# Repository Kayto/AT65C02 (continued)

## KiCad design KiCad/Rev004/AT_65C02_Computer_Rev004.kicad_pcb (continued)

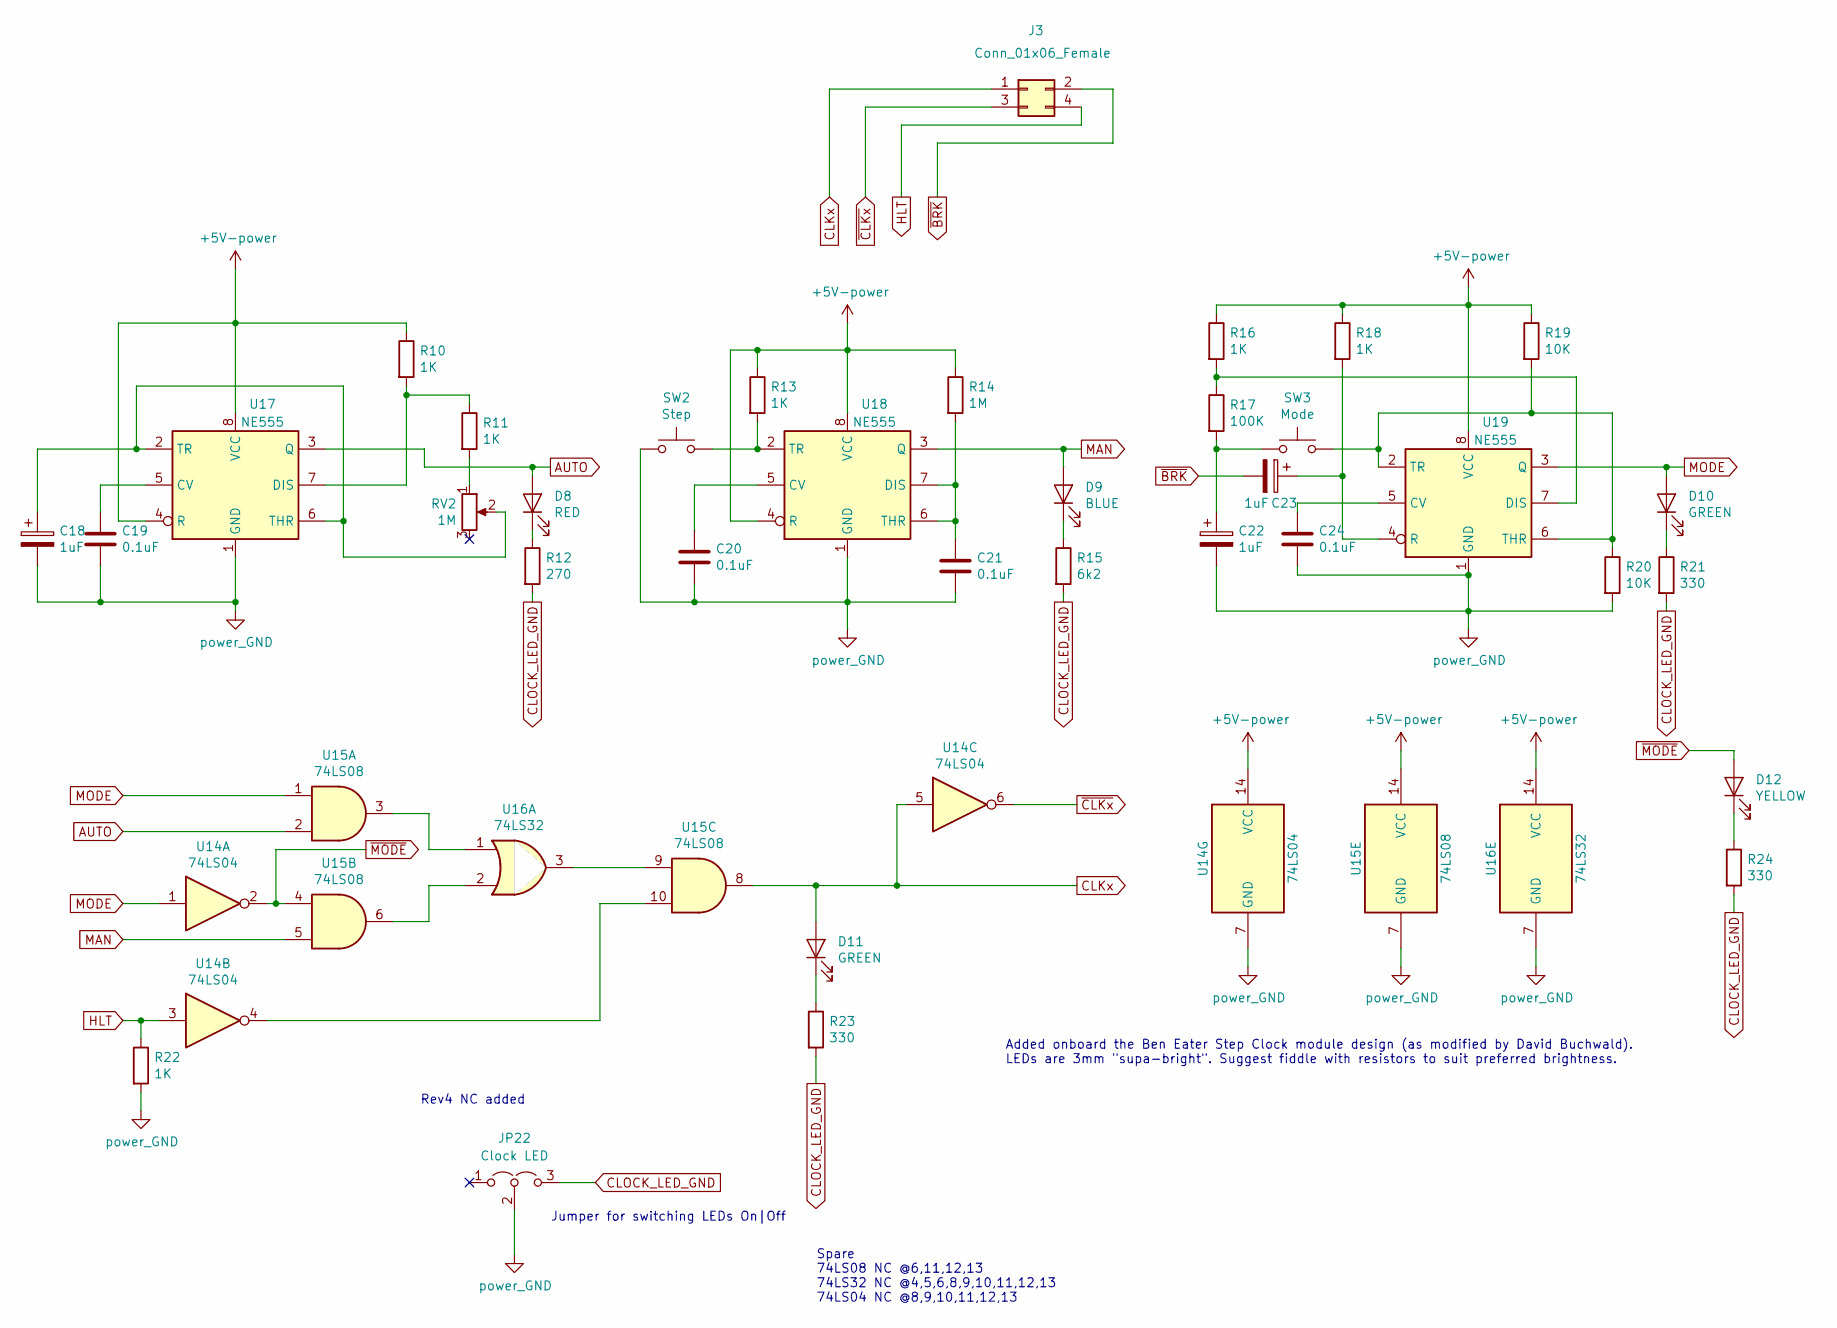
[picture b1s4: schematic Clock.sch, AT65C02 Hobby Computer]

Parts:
C18, C22, C23: 1uF; CP_Radial_D5.0mm_P2.50mm
C19, C20, C21, C24: 0.1uF; C_Disc_D3.4mm_W2.1mm_P2.50mm
D8: RED; LED_D3.0mm
D9: BLUE; LED_D3.0mm
D10, D11: GREEN; LED_D3.0mm
D12: YELLOW; LED_D3.0mm
J3: Conn_01x06_Female; PinSocket_2x02_P2.54mm_Vertical
JP22: Clock LED; PinHeader_1x03_P2.54mm_Vertical
R10, R11, R13, R16, R18, R22: 1K; R_Axial_DIN0207_L6.3mm_D2.5mm_P7.62mm_Horizontal
R12: 270; R_Axial_DIN0207_L6.3mm_D2.5mm_P7.62mm_Horizontal
R14: 1M; R_Axial_DIN0207_L6.3mm_D2.5mm_P7.62mm_Horizontal
R15: 6k2; R_Axial_DIN0207_L6.3mm_D2.5mm_P7.62mm_Horizontal
R17: 100K; R_Axial_DIN0207_L6.3mm_D2.5mm_P7.62mm_Horizontal
R19, R20: 10K; R_Axial_DIN0207_L6.3mm_D2.5mm_P7.62mm_Horizontal
R21, R23, R24: 330; R_Axial_DIN0207_L6.3mm_D2.5mm_P7.62mm_Horizontal
RV2: 1M; Potentiometer_Piher_PT-10-V10_Vertical
SW2: Step; SW_PUSH_6mm
SW3: Mode; SW_PUSH_6mm
U14: 74LS04; DIP-14_W7.62mm_Socket
U15: 74LS08; DIP-14_W7.62mm_Socket
U16: 74LS32; DIP-14_W7.62mm_Socket
U17, U18, U19: NE555; DIP-8_W7.62mm_Socket

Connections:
AUTO: D8.2 (A), U15.2, U17.3 (Q)
CLKx: D11.2 (A), J3.1, U14.5, U15.8; also elsewhere on the board
CLOCK_LED_GND: JP22.3 (B), R12.2, R15.2, R21.2, R23.2, R24.2
HLT: J3.4, R22.1, U14.3
MAN: D9.2 (A), U15.5, U18.3 (Q)
MODE: D10.2 (A), U14.1, U15.1, U19.3 (Q)
unnamed: C18.1, RV2.2, U17.2 (TR), U17.6 (THR)
unnamed: C19.1, U17.5 (CV)
unnamed: C20.1, U18.5 (CV)
unnamed: C21.1, R14.2, U18.6 (THR), U18.7 (DIS)
unnamed: C22.1, R17.2, SW3.1
unnamed: C23.1, R18.2, U19.4 (R)
unnamed: C24.1, U19.5 (CV)
unnamed: D8.1 (K), R12.1
unnamed: D9.1 (K), R15.1
unnamed: D10.1 (K), R21.1
unnamed: D11.1 (K), R23.1
unnamed: D12.1 (K), R24.1
unnamed: R10.2, R11.1, U17.7 (DIS)
unnamed: R11.2, RV2.1
unnamed: R13.2, SW2.2, U18.2 (TR)
unnamed: R16.2, R17.1, U19.7 (DIS)
unnamed: R19.2, R20.1, SW3.2, U19.2 (TR), U19.6 (THR)
unnamed: U14.4, U15.10
unnamed: U15.3, U16.1
unnamed: U15.6, U16.2
unnamed: U15.9, U16.3
~BRK: C23.2, J3.2
~CLKx: J3.3, U14.6
~MODE: D12.2 (A), U14.2, U15.4

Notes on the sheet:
Added onboard the Ben Eater Step Clock module design (as modified by David Buchwald). LEDs are 3mm "supa-bright". Suggest fiddle with resistors to suit preferred brightness.
Jumper for switching LEDs On|Off
Spare 74LS08 NC @6,11,12,13 74LS32 NC @4,5,6,8,9,10,11,12,13 74LS04 NC @8,9,10,11,12,13
Rev4 NC added

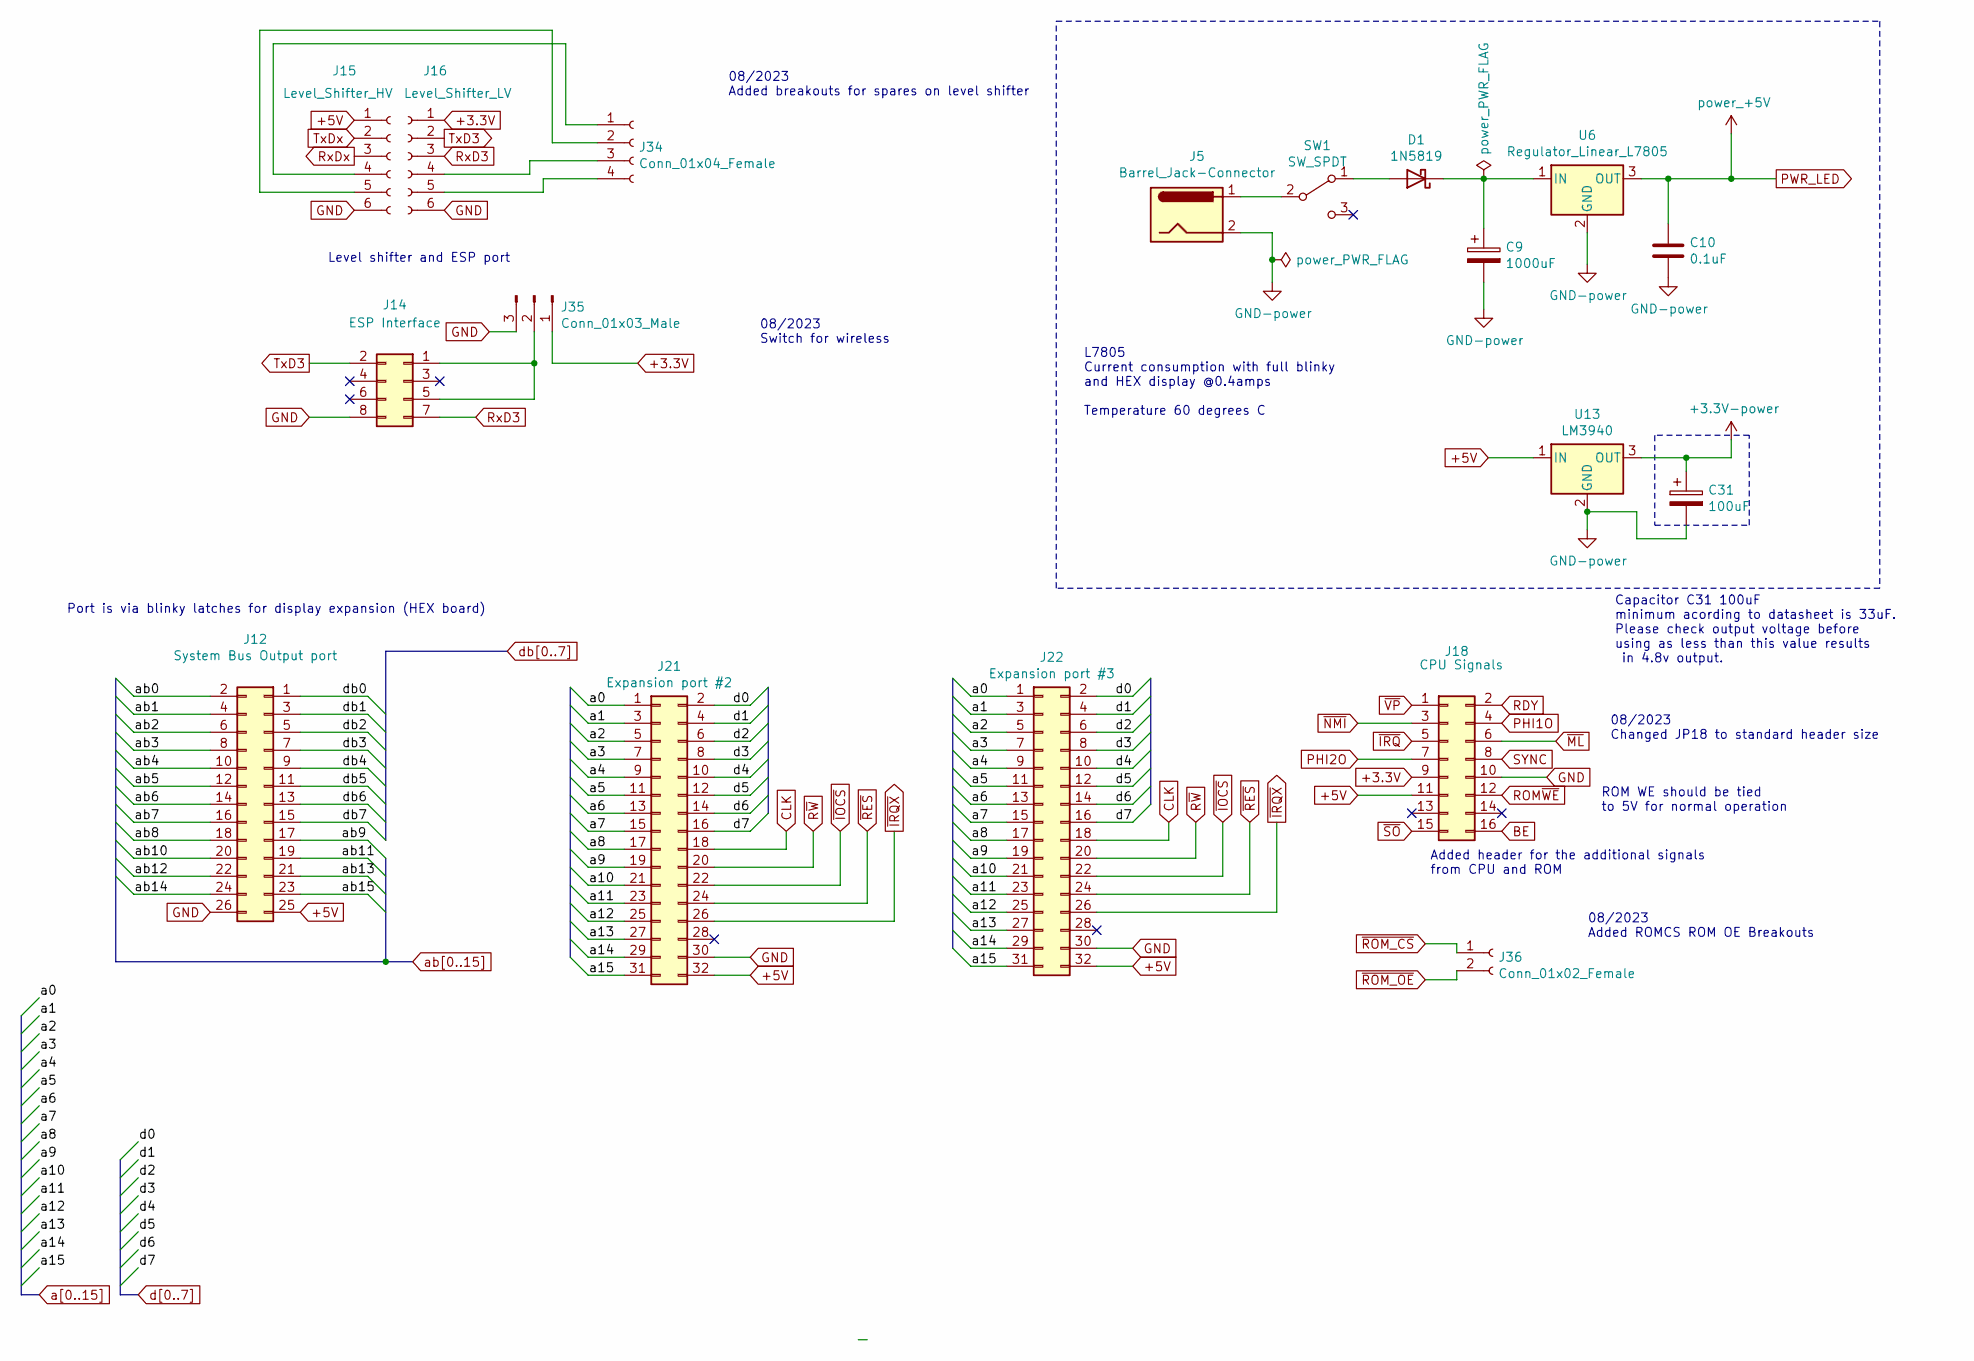
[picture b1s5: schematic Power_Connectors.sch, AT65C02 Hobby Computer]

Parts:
C9: 1000uF; CP_Radial_D10.0mm_P5.00mm
C10: 0.1uF; C_Disc_D3.4mm_W2.1mm_P2.50mm
C31: 100uF; CP_Radial_D5.0mm_P2.50mm
D1: 1N5819; D_DO-41_SOD81_P10.16mm_Horizontal
J5: Barrel_Jack-Connector; BarrelJack_Horizontal
J12: System Bus Output port; PinSocket_2x13_P2.54mm_Vertical
J14: ESP Interface; PinSocket_2x04_P2.54mm_Vertical
J15: Level_Shifter_HV; PinSocket_1x06_P2.54mm_Vertical
J16: Level_Shifter_LV; PinSocket_1x06_P2.54mm_Vertical
J18: CPU Signals; PinSocket_2x08_P2.54mm_Vertical
J21: Expansion port #2; PinSocket_2x16_P2.54mm_Vertical
J22: Expansion port #3; PinSocket_2x16_P2.54mm_Vertical
J34: Conn_01x04_Female; PinSocket_1x04_P2.54mm_Vertical
J35: Conn_01x03_Male; PinHeader_1x03_P2.54mm_Vertical
J36: Conn_01x02_Female; PinSocket_1x02_P2.54mm_Vertical
SW1: SW_SPDT; PinHeader_1x03_P2.54mm_Vertical
U6: Regulator_Linear_L7805; TO-220-3_Horizontal_TabDown
U13: LM3940; TO-220-3_Horizontal_TabDown

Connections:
BE: J18.16; also elsewhere on the board
CLK: J21.18, J22.18; also elsewhere on the board
unnamed: C9.1, D1.1 (K), U6.1 (IN)
unnamed: D1.2 (A), SW1.1 (A)
unnamed: J5.1, SW1.2 (B)
unnamed: J14.1, J14.5, J35.2
unnamed: J15.4, J34.1
unnamed: J15.5, J34.2
unnamed: J16.4, J34.3
unnamed: J16.5, J34.4
PHI1O: J18.4; also elsewhere on the board
PHI2O: J18.7; also elsewhere on the board
RDY: J18.2; also elsewhere on the board
ROM~WE: J18.12; also elsewhere on the board
RxD: J15.3; also elsewhere on the board
RxD3: J14.7, J16.3
R~W: J21.20, J22.20; also elsewhere on the board
SYNC: J18.8; also elsewhere on the board
TxD: J15.2; also elsewhere on the board
TxD3: J14.2, J16.2
a0: J21.1, J22.1; also elsewhere on the board
a1: J21.3, J22.3; also elsewhere on the board
a2: J21.5, J22.5; also elsewhere on the board
a3: J21.7, J22.7; also elsewhere on the board
a4: J21.9, J22.9; also elsewhere on the board
a5: J21.11, J22.11; also elsewhere on the board
a6: J21.13, J22.13; also elsewhere on the board
a7: J21.15, J22.15; also elsewhere on the board
a8: J21.17, J22.17; also elsewhere on the board
a9: J21.19, J22.19; also elsewhere on the board
a10: J21.21, J22.21; also elsewhere on the board
a11: J21.23, J22.23; also elsewhere on the board
a12: J21.25, J22.25; also elsewhere on the board
a13: J21.27, J22.27; also elsewhere on the board
a14: J21.29, J22.29; also elsewhere on the board
a15: J21.31, J22.31; also elsewhere on the board
ab0: J12.2; also elsewhere on the board
ab1: J12.4; also elsewhere on the board
ab2: J12.6; also elsewhere on the board
ab3: J12.8; also elsewhere on the board
ab4: J12.10; also elsewhere on the board
ab5: J12.12; also elsewhere on the board
ab6: J12.14; also elsewhere on the board
ab7: J12.16; also elsewhere on the board
ab8: J12.18; also elsewhere on the board
ab9: J12.17; also elsewhere on the board
ab10: J12.20; also elsewhere on the board
ab11: J12.19; also elsewhere on the board
ab12: J12.22; also elsewhere on the board
ab13: J12.21; also elsewhere on the board
ab14: J12.24; also elsewhere on the board
ab15: J12.23; also elsewhere on the board
d0: J21.2, J22.2; also elsewhere on the board
d1: J21.4, J22.4; also elsewhere on the board
d2: J21.6, J22.6; also elsewhere on the board
d3: J21.8, J22.8; also elsewhere on the board
d4: J21.10, J22.10; also elsewhere on the board
d5: J21.12, J22.12; also elsewhere on the board
d6: J21.14, J22.14; also elsewhere on the board
d7: J21.16, J22.16; also elsewhere on the board
db0: J12.1; also elsewhere on the board
db1: J12.3; also elsewhere on the board
db2: J12.5; also elsewhere on the board
db3: J12.7; also elsewhere on the board
db4: J12.9; also elsewhere on the board
db5: J12.11; also elsewhere on the board
db6: J12.13; also elsewhere on the board
db7: J12.15; also elsewhere on the board
~IOCS: J21.22, J22.22; also elsewhere on the board
~IRQ: J18.5; also elsewhere on the board
~IRQX: J21.26, J22.26; also elsewhere on the board
~ML: J18.6; also elsewhere on the board
~NMI: J18.3; also elsewhere on the board
~RES: J21.24, J22.24; also elsewhere on the board
~ROM_CS: J36.1; also elsewhere on the board
~ROM_OE: J36.2; also elsewhere on the board
~SO: J18.15; also elsewhere on the board
~VP: J18.1; also elsewhere on the board

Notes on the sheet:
Port is via blinky latches for display expansion (HEX board)
Level shifter and ESP port
L7805 Current consumption with full blinky and HEX display @0.4amps Temperature 60 degrees C
Added header for the additional signals from CPU and ROM
Capacitor C31 100uF minimum acording to datasheet is 33uF. Please check output voltage before using as less than this value results in 4.8v output.
ROM WE should be tied to 5V for normal operation
08/2023 Switch for wireless
08/2023 Added breakouts for spares on level shifter
08/2023 Changed JP18 to standard header size
08/2023 Added ROMCS ROM OE Breakouts

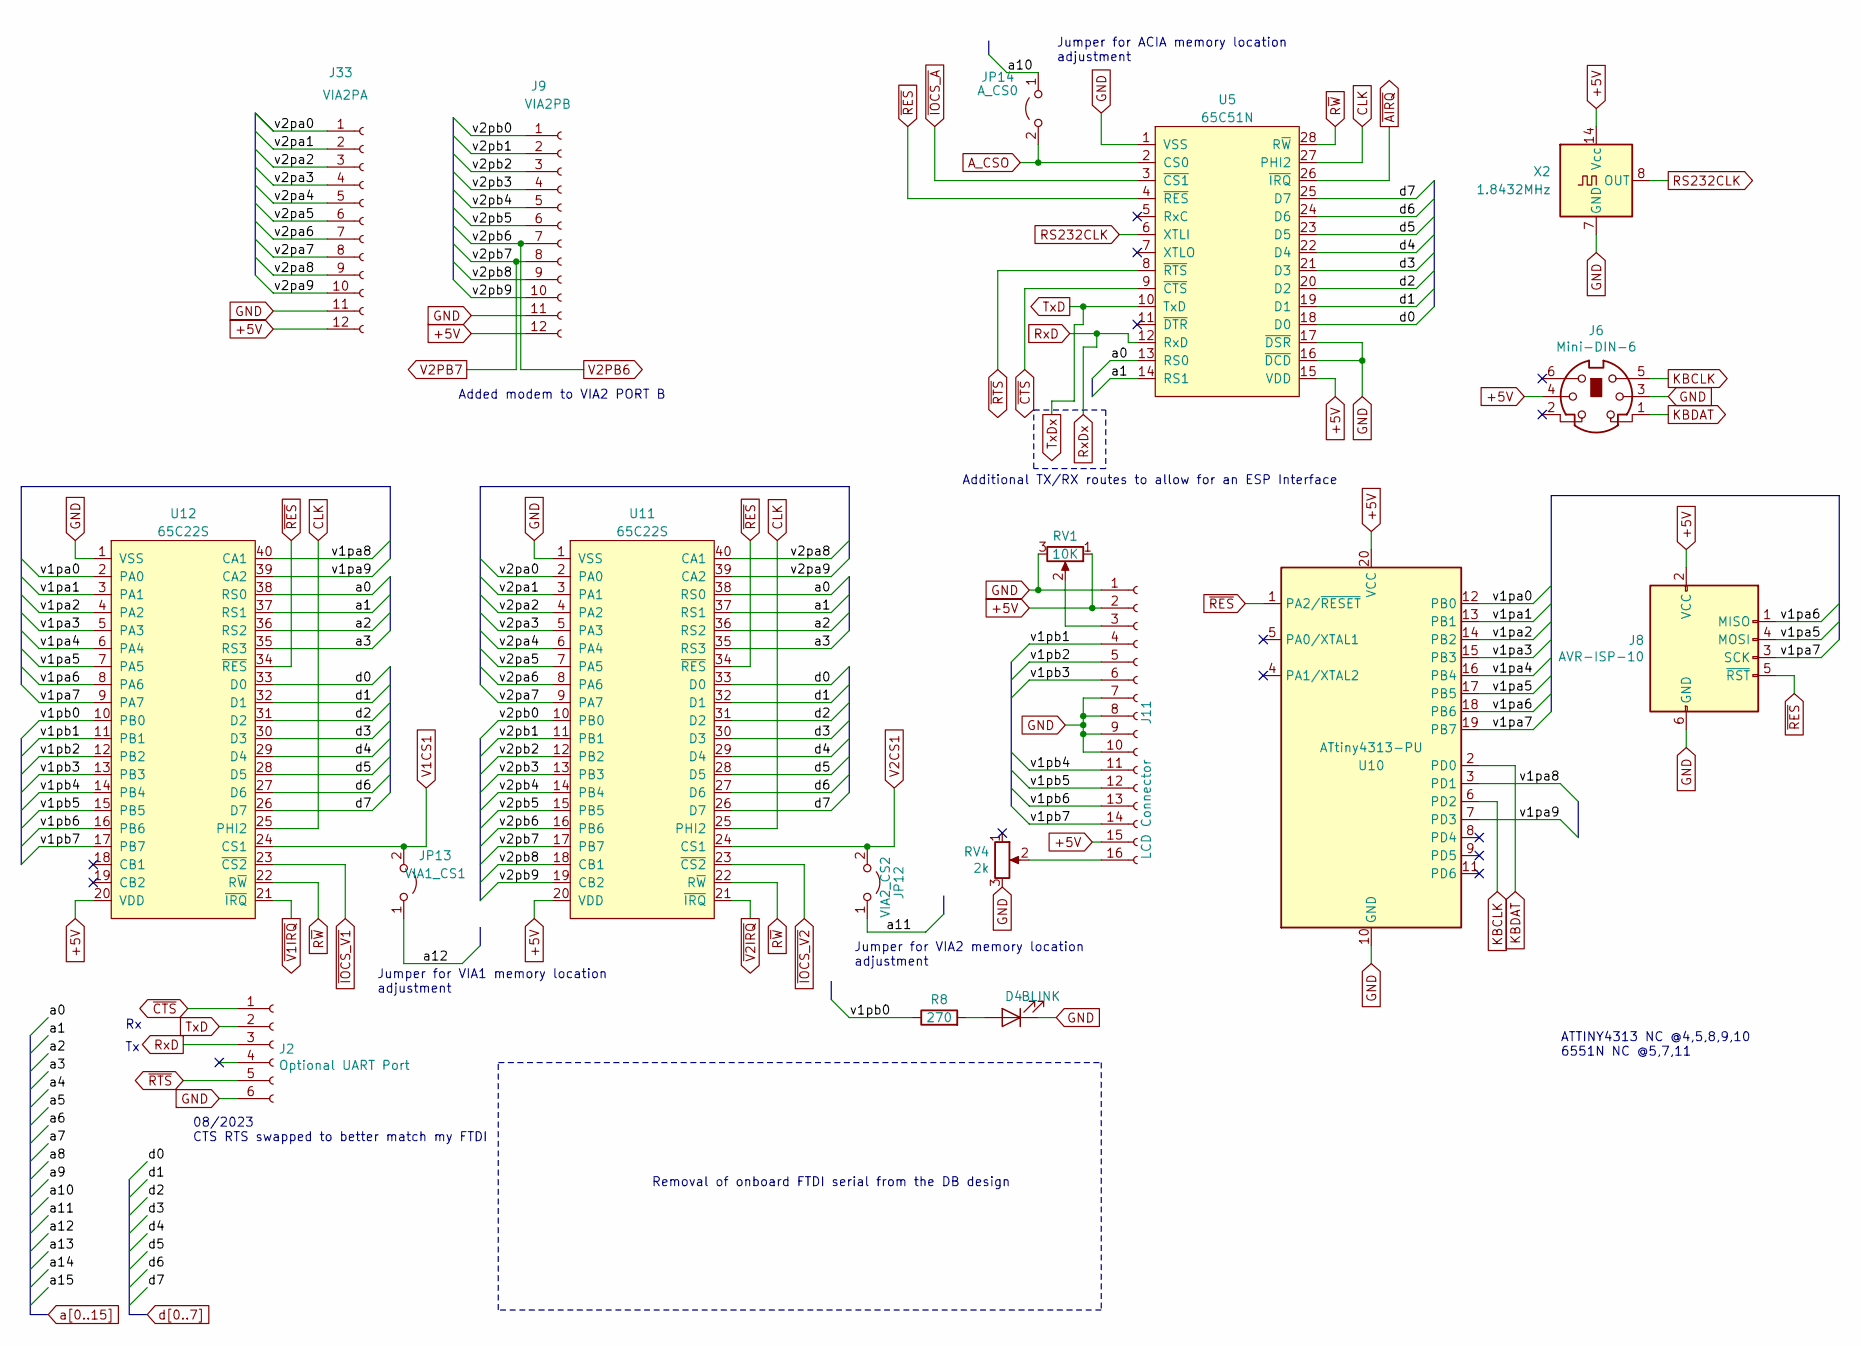
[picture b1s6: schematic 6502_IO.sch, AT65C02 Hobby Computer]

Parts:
D4: BLINK; LED_D3.0mm
J2: Optional UART Port; PinSocket_1x06_P2.54mm_Vertical
J6: Mini-DIN-6; mini_din-6
J8: AVR-ISP-10; PinHeader_2x03_P2.54mm_Vertical
J9: VIA2PB; PinSocket_1x12_P2.54mm_Vertical
J11: LCD Connector; PinSocket_1x16_P2.54mm_Vertical
J33: VIA2PA; PinSocket_1x12_P2.54mm_Vertical
JP12: VIA2_CS2; PinHeader_1x02_P2.54mm_Vertical
JP13: VIA1_CS1; PinHeader_1x02_P2.54mm_Vertical
JP14: A_CS0; PinHeader_1x02_P2.54mm_Vertical
R8: 270; R_Axial_DIN0207_L6.3mm_D2.5mm_P7.62mm_Horizontal
RV1: 10K; Potentiometer_Piher_PT-10-V10_Vertical
RV4: 2k; Potentiometer_Piher_PT-10-V10_Vertical
U5: 65C51N; DIP-28_W15.24mm_Socket
U10: ATtiny4313-PU; DIP-20_W7.62mm_Socket
U11, U12: 65C22S; DIP-40_W15.24mm_Socket
X2: 1.8432MHz; Oscillator_DIP-14

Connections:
/6502 Peripherals/v1pa0: U10.12 (PB0), U12.2 (PA0)
/6502 Peripherals/v1pa1: U10.13 (PB1), U12.3 (PA1)
/6502 Peripherals/v1pa2: U10.14 (PB2), U12.4 (PA2)
/6502 Peripherals/v1pa3: U10.15 (PB3), U12.5 (PA3)
/6502 Peripherals/v1pa4: U10.16 (PB4), U12.6 (PA4)
/6502 Peripherals/v1pa5: J8.4 (MOSI), U10.17 (PB5), U12.7 (PA5)
/6502 Peripherals/v1pa6: J8.1 (MISO), U10.18 (PB6), U12.8 (PA6)
/6502 Peripherals/v1pa7: J8.3 (SCK), U10.19 (PB7), U12.9 (PA7)
/6502 Peripherals/v1pa8: U10.3 (PD1), U12.40 (CA1)
/6502 Peripherals/v1pa9: U10.7 (PD3), U12.39 (CA2)
/6502 Peripherals/v1pb0: R8.1, U12.10 (PB0)
/6502 Peripherals/v1pb1: J11.4, U12.11 (PB1)
/6502 Peripherals/v1pb2: J11.5, U12.12 (PB2)
/6502 Peripherals/v1pb3: J11.6, U12.13 (PB3)
/6502 Peripherals/v1pb4: J11.11, U12.14 (PB4)
/6502 Peripherals/v1pb5: J11.12, U12.15 (PB5)
/6502 Peripherals/v1pb6: J11.13, U12.16 (PB6)
/6502 Peripherals/v1pb7: J11.14, U12.17 (PB7)
/6502 Peripherals/v2pa0: J33.1, U11.2 (PA0)
/6502 Peripherals/v2pa1: J33.2, U11.3 (PA1)
/6502 Peripherals/v2pa2: J33.3, U11.4 (PA2)
/6502 Peripherals/v2pa3: J33.4, U11.5 (PA3)
/6502 Peripherals/v2pa4: J33.5, U11.6 (PA4)
/6502 Peripherals/v2pa5: J33.6, U11.7 (PA5)
/6502 Peripherals/v2pa6: J33.7, U11.8 (PA6)
/6502 Peripherals/v2pa7: J33.8, U11.9 (PA7)
/6502 Peripherals/v2pa8: J33.9, U11.40 (CA1)
/6502 Peripherals/v2pa9: J33.10, U11.39 (CA2)
/6502 Peripherals/v2pb0: J9.1, U11.10 (PB0)
/6502 Peripherals/v2pb1: J9.2, U11.11 (PB1)
/6502 Peripherals/v2pb2: J9.3, U11.12 (PB2)
/6502 Peripherals/v2pb3: J9.4, U11.13 (PB3)
/6502 Peripherals/v2pb4: J9.5, U11.14 (PB4)
/6502 Peripherals/v2pb5: J9.6, U11.15 (PB5)
/6502 Peripherals/v2pb8: J9.9, U11.18 (CB1)
/6502 Peripherals/v2pb9: J9.10, U11.19 (CB2)
A_CSO: JP14.2 (B), U5.2 (CS0)
CLK: U5.27 (PHI2), U11.25 (PHI2), U12.25 (PHI2); also elsewhere on the board
KBCLK: J6.5, U10.6 (PD2)
KBDAT: J6.1, U10.2 (PD0)
unnamed: D4.2 (A), R8.2
unnamed: J11.3, RV1.2
unnamed: J11.16, RV4.2
RS232CLK: U5.6 (XTLI), X2.8 (OUT)
RxD: J2.3, U5.12 (RxD); also elsewhere on the board
R~W: U5.28 (R~W), U11.22 (R~W), U12.22 (R~W); also elsewhere on the board
TxD: J2.2, U5.10 (TxD); also elsewhere on the board
V1CS1: JP13.2 (B), U12.24 (CS1)
V2CS1: JP12.2 (B), U11.24 (CS1)
V2PB6: J9.7, U11.16 (PB6); also elsewhere on the board
V2PB7: J9.8, U11.17 (PB7); also elsewhere on the board
a0: U5.13 (RS0), U11.38 (RS0), U12.38 (RS0); also elsewhere on the board
a1: U5.14 (RS1), U11.37 (RS1), U12.37 (RS1); also elsewhere on the board
a2: U11.36 (RS2), U12.36 (RS2); also elsewhere on the board
a3: U11.35 (RS3), U12.35 (RS3); also elsewhere on the board
a10: JP14.1 (A); also elsewhere on the board
a11: JP12.1 (A); also elsewhere on the board
a12: JP13.1 (A); also elsewhere on the board
d0: U5.18 (D0), U11.33 (D0), U12.33 (D0); also elsewhere on the board
d1: U5.19 (D1), U11.32 (D1), U12.32 (D1); also elsewhere on the board
d2: U5.20 (D2), U11.31 (D2), U12.31 (D2); also elsewhere on the board
d3: U5.21 (D3), U11.30 (D3), U12.30 (D3); also elsewhere on the board
d4: U5.22 (D4), U11.29 (D4), U12.29 (D4); also elsewhere on the board
d5: U5.23 (D5), U11.28 (D5), U12.28 (D5); also elsewhere on the board
d6: U5.24 (D6), U11.27 (D6), U12.27 (D6); also elsewhere on the board
d7: U5.25 (D7), U11.26 (D7), U12.26 (D7); also elsewhere on the board
~AIRQ: U5.26 (~IRQ); also elsewhere on the board
~CTS: J2.1, U5.9 (~CTS)
~IOCS_A: U5.3 (~CS1); also elsewhere on the board
~IOCS_V1: U12.23 (~CS2); also elsewhere on the board
~IOCS_V2: U11.23 (~CS2); also elsewhere on the board
~RES: J8.5 (~RST), U5.4 (~RES), U10.1 (PA2/~RESET), U11.34 (~RES), U12.34 (~RES); also elsewhere on the board
~RTS: J2.5, U5.8 (~RTS)
~V1IRQ: U12.21 (~IRQ); also elsewhere on the board
~V2IRQ: U11.21 (~IRQ); also elsewhere on the board

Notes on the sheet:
Added modem to VIA2 PORT B
Additional TX/RX routes to allow for an ESP Interface
Removal of onboard FTDI serial from the DB design
Jumper for VIA1 memory location adjustment
Jumper for VIA2 memory location adjustment
Jumper for ACIA memory location adjustment
ATTINY4313 NC @4,5,8,9,10 6551N NC @5,7,11
08/2023 CTS RTS swapped to better match my FTDI

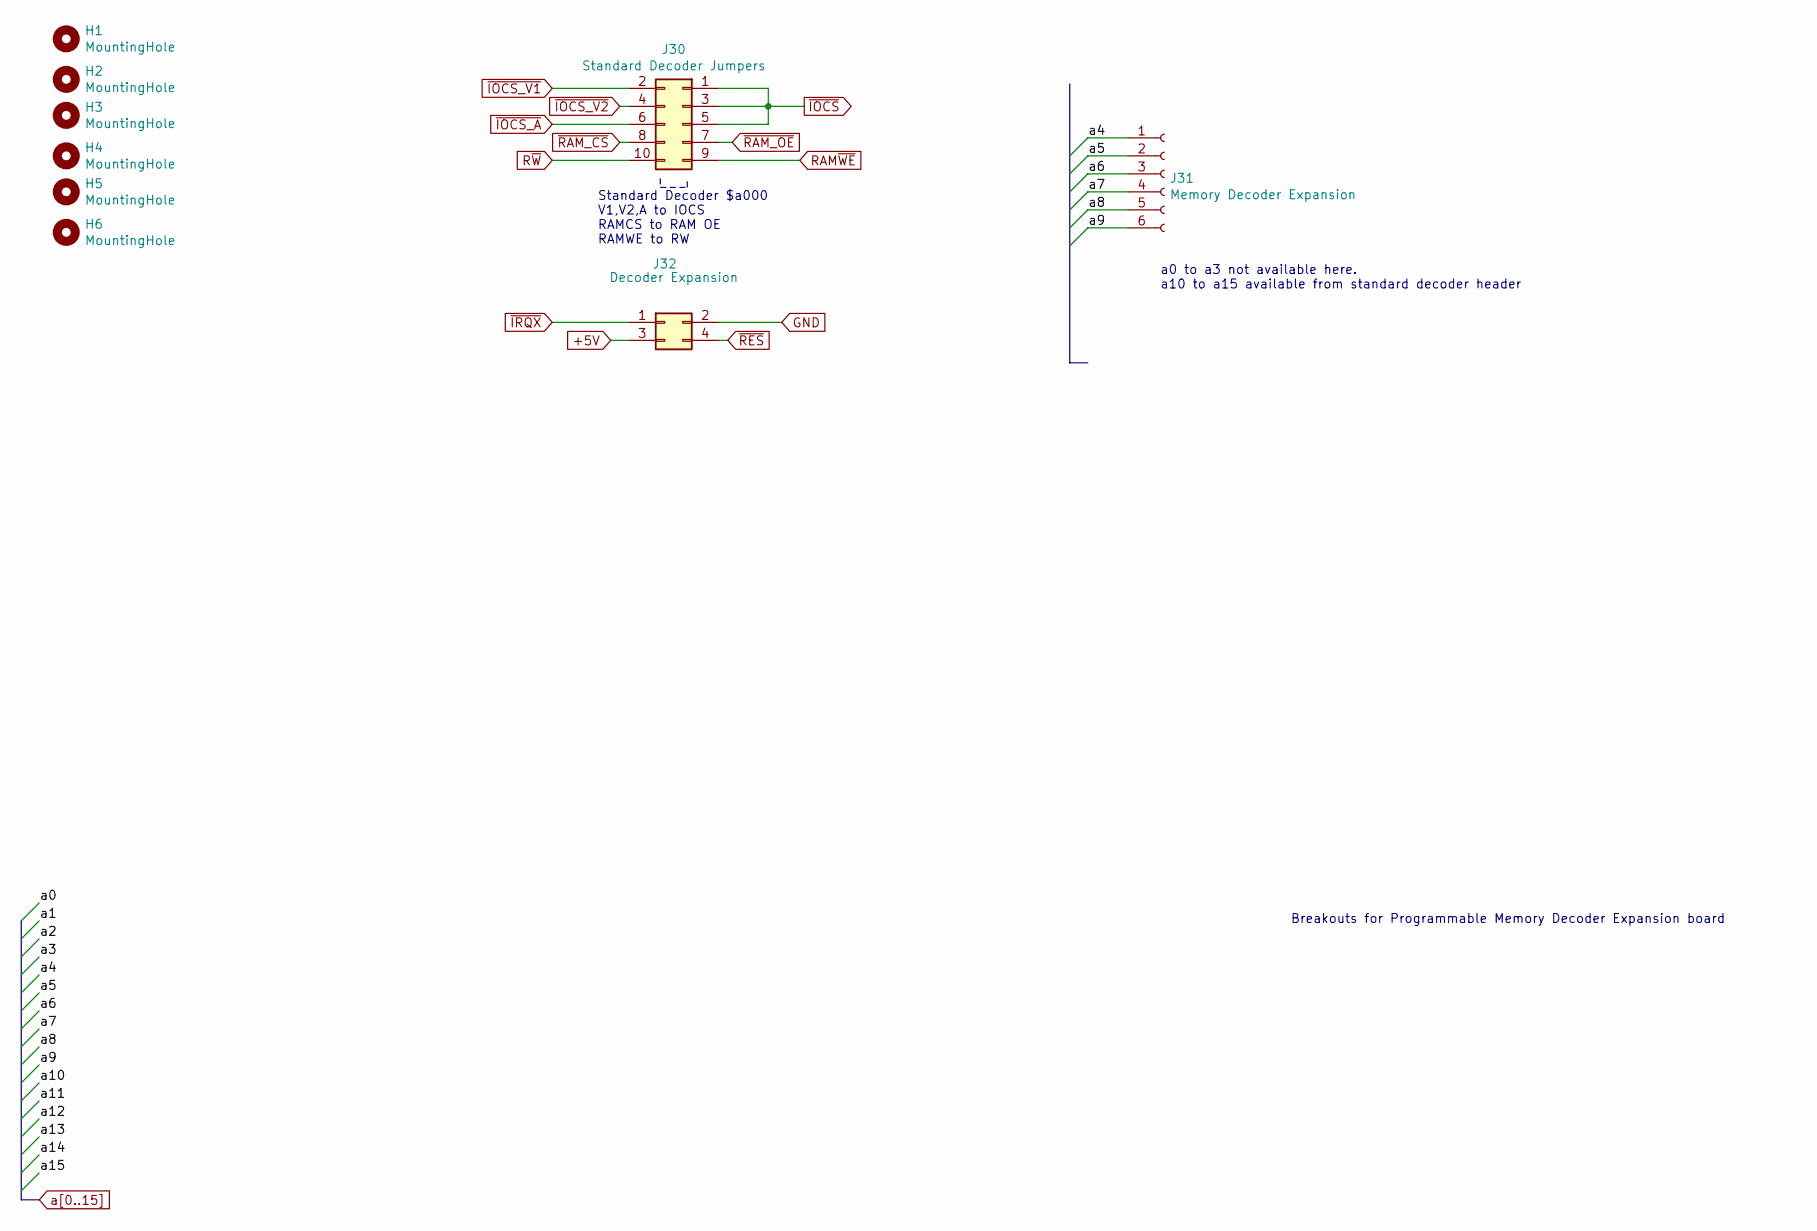
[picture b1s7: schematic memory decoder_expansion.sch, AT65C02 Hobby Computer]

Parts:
H1, H2, H3, H4, H5, H6: MountingHole; MountingHole_3mm_Pad
J30: Standard Decoder Jumpers; PinHeader_2x05_P2.54mm_Vertical
J31: Memory Decoder Expansion; PinSocket_1x06_P2.54mm_Vertical
J32: Decoder Expansion; PinSocket_2x02_P2.54mm_Vertical

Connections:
RAM~WE~: J30.9; also elsewhere on the board
R~W: J30.10; also elsewhere on the board
a4: J31.1; also elsewhere on the board
a5: J31.2; also elsewhere on the board
a6: J31.3; also elsewhere on the board
a7: J31.4; also elsewhere on the board
a8: J31.5; also elsewhere on the board
a9: J31.6; also elsewhere on the board
~IOCS: J30.1, J30.3, J30.5; also elsewhere on the board
~IOCS_A: J30.6; also elsewhere on the board
~IOCS_V1: J30.2; also elsewhere on the board
~IOCS_V2: J30.4; also elsewhere on the board
~IRQX: J32.1; also elsewhere on the board
~RAM_CS: J30.8; also elsewhere on the board
~RAM_OE: J30.7; also elsewhere on the board
~RES: J32.4; also elsewhere on the board

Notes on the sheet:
Standard Decoder $a000 V1,V2,A to IOCS RAMCS to RAM OE RAMWE to RW
Breakouts for Programmable Memory Decoder Expansion board
a0 to a3 not available here. a10 to a15 available from standard decoder header

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
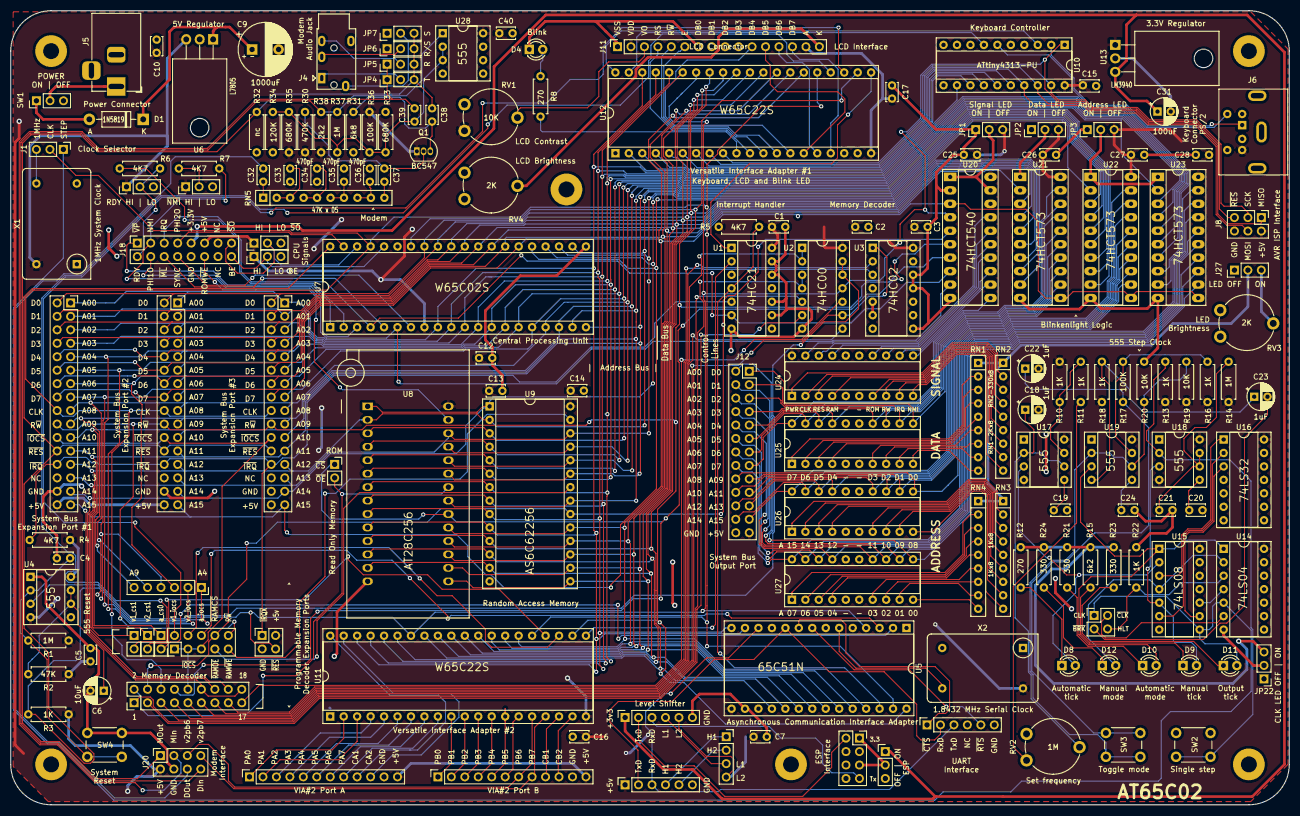
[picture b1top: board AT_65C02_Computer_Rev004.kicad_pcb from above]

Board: 2 copper layers, 241.3 x 149.9 mm, 167 parts (0 on the bottom side), 245 nets.

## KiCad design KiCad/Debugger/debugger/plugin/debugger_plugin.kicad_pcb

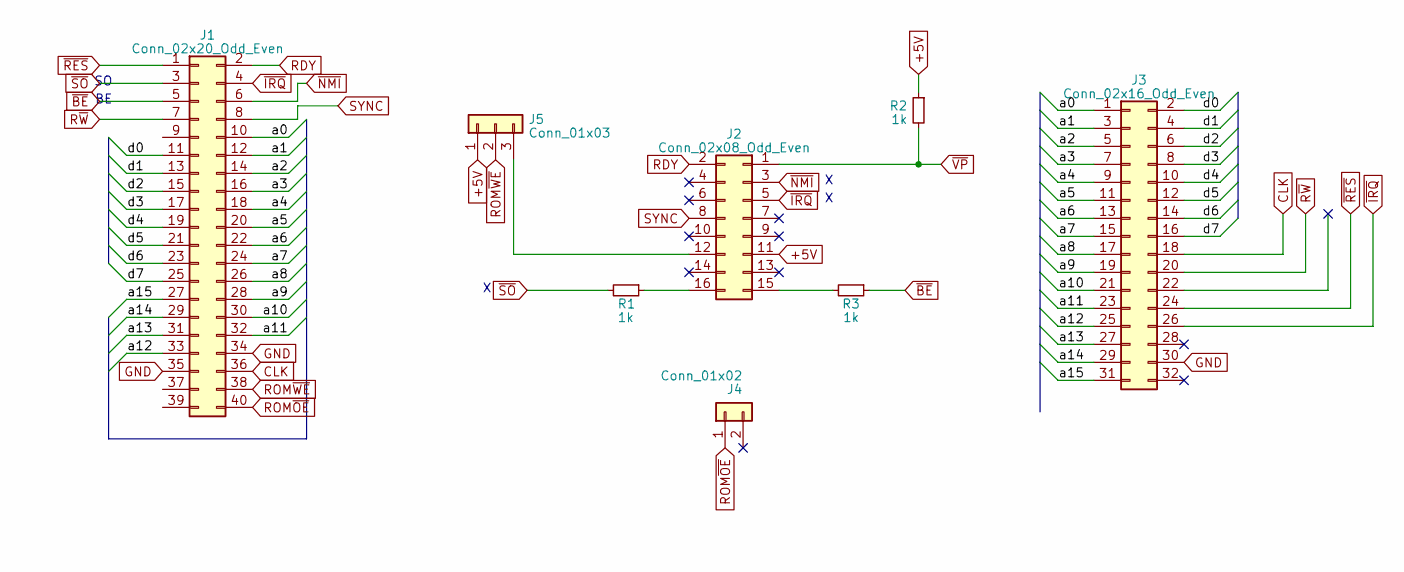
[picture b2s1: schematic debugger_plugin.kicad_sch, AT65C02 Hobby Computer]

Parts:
J1: Conn_02x20_Odd_Even; IDC-Header_2x20_P2.54mm_Vertical
J2: Conn_02x08_Odd_Even; PinHeader_2x08_P2.54mm_Vertical
J3: Conn_02x16_Odd_Even; PinHeader_2x16_P2.54mm_Vertical
J4: Conn_01x02; PinHeader_1x02_P2.54mm_Vertical
J5: Conn_01x03; PinHeader_1x03_P2.54mm_Vertical
R1, R2, R3: 1k; R_Axial_DIN0207_L6.3mm_D2.5mm_P7.62mm_Horizontal

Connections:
+5V: J2.11, J5.1, R2.1
/a0: J1.10, J3.1
/a1: J1.12, J3.3
/a2: J1.14, J3.5
/a3: J1.16, J3.7
/a4: J1.18, J3.9
/a5: J1.20, J3.11
/a6: J1.22, J3.13
/a7: J1.24, J3.15
/a8: J1.26, J3.17
/a9: J1.28, J3.19
/a10: J1.30, J3.21
/a11: J1.32, J3.23
/a12: J1.33, J3.25
/a13: J1.31, J3.27
/a14: J1.29, J3.29
/a15: J1.27, J3.31
/d0: J1.11, J3.2
/d1: J1.13, J3.4
/d2: J1.15, J3.6
/d3: J1.17, J3.8
/d4: J1.19, J3.10
/d5: J1.21, J3.12
/d6: J1.23, J3.14
/d7: J1.25, J3.16
CLK: J1.36, J3.18
GND: J1.34, J1.35, J3.30
unnamed: J2.12, J5.3
unnamed: J2.15, R3.2
unnamed: J2.16, R1.1
RDY: J1.2, J2.2
ROM~OE: J1.40, J4.1
ROM~WE: J1.38, J5.2
R~W: J1.7, J3.20
SYNC: J1.8, J2.8
~BE: J1.5, R3.1
~IRQ: J1.4, J2.5, J3.26
~NMI: J1.6, J2.3
~RES: J1.1, J3.24
~SO: J1.3, R1.2
~VP: J2.1, R2.2

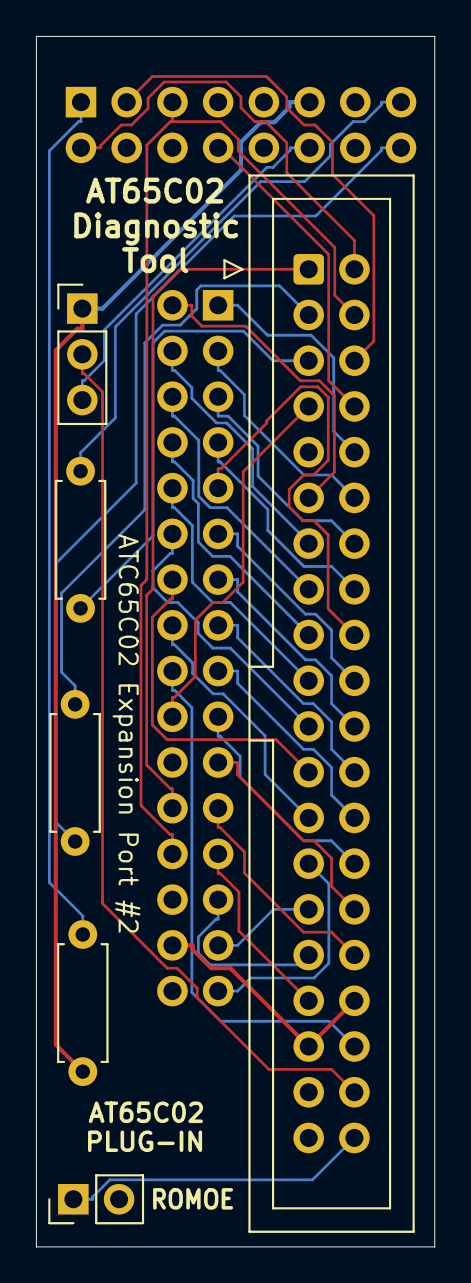
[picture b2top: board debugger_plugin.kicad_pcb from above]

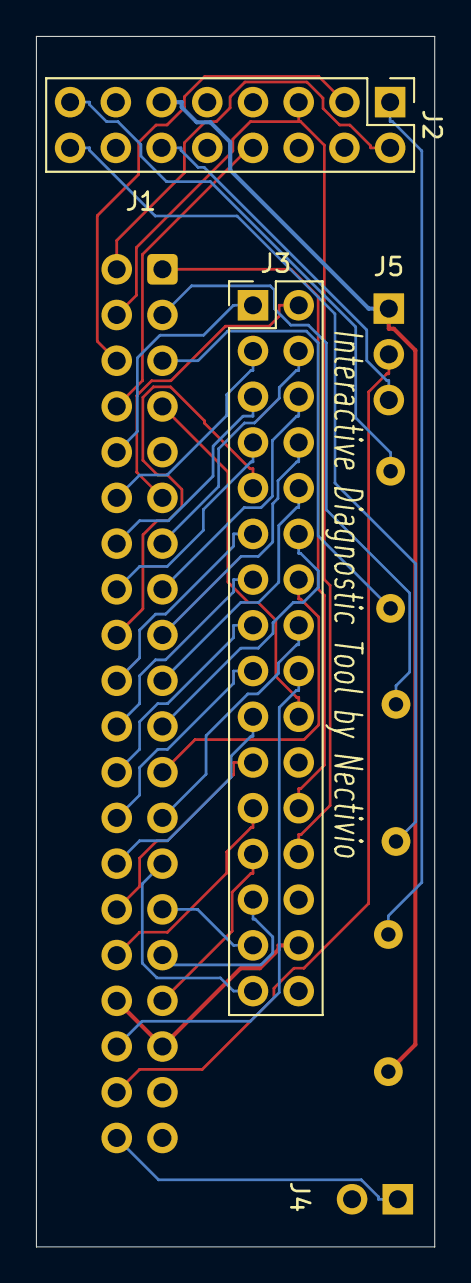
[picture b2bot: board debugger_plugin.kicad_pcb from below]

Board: 2 copper layers, 22.1 x 67.2 mm, 8 parts (2 on the bottom side), 41 nets.
